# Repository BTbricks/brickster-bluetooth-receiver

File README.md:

# BricksTer &ndash; Bluetooth Receiver

&nbsp;&nbsp;&nbsp;

The BricksTer Bluetooth Receiver lets you wirelessly control your LEGO creations from a smart phone, tablet, or PC. It is compatible with the NXT programmable brick. This repository houses the Eagle CAD schematic and design files for the printed circuit board along with the firmware for the receiver.

## Getting Started

### Part List

Components can be ordered from any distributor (e.g. DigiKey, Mouser, etc).  
[Please see the Bill of Materials for the list of components.](https://github.com/BTbricks/brickster-bluetooth-receiver/blob/master/8884bt%20Remote%20Control%20Receiver/board/BOM.md)

The rev. 2 board can be purchased from OSH Park.  
[Click here to view the OSH Park project page.](https://oshpark.com/shared_projects/jNrizzs2)

### Programming the Board

Once your board is soldered, use the Arduino IDE to load the firmware onto the microcontroller.  
The IDE is available for free and can be downloaded from http://arduino.cc/main/software

#### Setting up the Arduino Environment

The microcontroller is an ATtiny84, which is not regularly supported by the Arduino IDE.  
[Please visit the Arduino support page to learn more about using Arduino with the ATtiny84.](http://playground.arduino.cc/Main/ArduinoOnOtherAtmelChips)

Download the [Attiny 44/45/84/85 files](https://github.com/damellis/attiny/archive/master.zip) and extract them to `{ARDUINO}/hardware/`, where `{ARDUINO}` represents the directory into which the Arduino IDE and supporting files have been installed. Once completed, your directory should look like this:

```
{ARDUINO}
└-hardware
  └-attiny
    ├-boards.txt
    └-variants
      ├-tiny8
      | └-pins_arduino.h
      └-tiny14
        └-pins_arduino.h
```

#### Burning the "Bootloader"

The ATtiny84 comes from the factory running on an internal 1 MHz clock. In order to run the BricksTer firmware, the ATtiny84 must be told to use its interal 8 MHz clock.

* Connect your board to your computer via the programmer
* Apply power to the power-in Power Functions wire
* Open the Arduino IDE
* Ensure you have selected the proper serial port (`Tools > Serial Port`) and can communicate with the microcontroller
* Select `Tools > Board > ATtiny84 (internal 8 Mhz clock)`
* Select `Tools > Burn Bootloader`
* Wait for the programmer to finish, the IDE should display a success message

#### Loading the Firmware

* Connect your board to your computer via the programmer
* Apply power to the power-in Power Functions wire
* Open the Arduino IDE
* Ensure you have selected the proper serial port (`Tools > Serial Port`) and can communicate with the microcontroller
* Select `Tools > Board > ATtiny84 (internal 8 Mhz clock)`
* Open the firmware file, [`brickster8884bt.ino`](https://github.com/BTbricks/brickster-bluetooth-receiver/blob/master/8884bt%20Remote%20Control%20Receiver/firmware/brickster8884bt.ino)
* Click the Upload button on the Arduino IDE (circle with a right-pointing arrow)
* Wait for the the IDE and programmer to finish, the IDE should display a success message

Note: Use of a Atmel AVRISPmk2 programmer is strongly advised. Other programmers have been known to work, but we can only provide support for the AVRISPmk2.

### File Formats

Design files are created in CadSoft Eagle PCB Design Software.  
A free version of the software can be downloaded from www.cadsoftusa.com

&nbsp;&nbsp;&nbsp;

## Distribution License

Where possible, this project uses the MIT license. [Please see the license file for full details.](https://github.com/BTbricks/brickster-bluetooth-receiver/blob/master/LICENSE)

## Contributing

The project is open to all issues and pull requests.  
If you have any other questions or feedback, please [contact the project maintainers](https://github.com/orgs/BTbricks/members).

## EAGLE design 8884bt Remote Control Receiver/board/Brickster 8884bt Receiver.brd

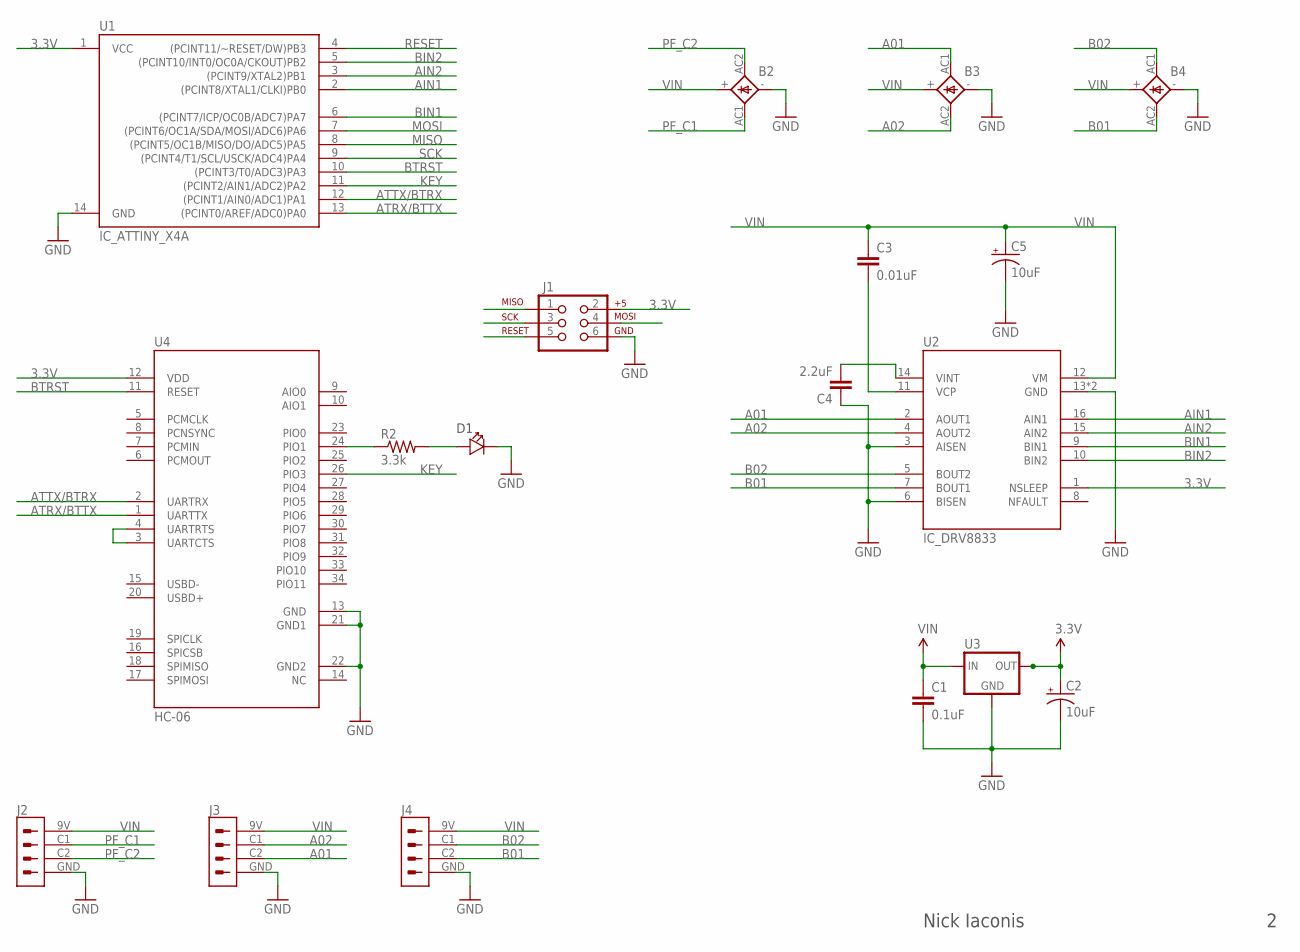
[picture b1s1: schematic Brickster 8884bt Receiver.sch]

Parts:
B2, B3, B4: B_CDBHM240L-HF; MBS-2
C1: 0.1uF; 0805
C2, C5: 10uF; 1206
C3: 0.01uF; 0805
C4: 2.2uF; 0805
D1: LED0805; 0805_POL
J1: AVR_SPI_PRG_6NS; 2X3-NS
J2, J3, J4: CON_PF_SMD; SMD_PF
R2: 3.3k; 0805
U1: IC_ATTINY_X4A; 14S1
U2: IC_DRV8833; PWP_R-PDSO-G16
U3: IC_RT9164A; SOT223
U4: HC-06; BLUETOOTH_SMD

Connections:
3.3V: C2.1 (+), J1.2, U1.1 (VCC), U2.1 (NSLEEP), U3.2 (OUT), U3.4, U4.12 (VDD)
A01: B3.AC1, J3.C2, U2.2 (AOUT1)
A02: B3.AC2, J3.C1, U2.4 (AOUT2)
AIN1: U1.2 ((PCINT8/XTAL1/CLKI)PB0), U2.16 (AIN1)
AIN2: U1.3 ((PCINT9/XTAL2)PB1), U2.15 (AIN2)
ATRX/BTTX: U1.13 ((PCINT0/AREF/ADC0)PA0), U4.1 (UARTTX)
ATTX/BTRX: U1.12 ((PCINT1/AIN0/ADC1)PA1), U4.2 (UARTRX)
B01: B4.AC2, J4.C2, U2.7 (BOUT1)
B02: B4.AC1, J4.C1, U2.5 (BOUT2)
BIN1: U1.6 ((PCINT7/ICP/OC0B/ADC7)PA7), U2.9 (BIN1)
BIN2: U1.5 ((PCINT10/INT0/OC0A/CKOUT)PB2), U2.10 (BIN2)
BTRST: U1.10 ((PCINT3/T0/ADC3)PA3), U4.11 (RESET)
GND: B2.-, B3.-, B4.-, C1.P$2 (2), C2.2 (-), C4.P$1 (1), C5.2 (-), D1.P$1, J1.6, J2.GND, J3.GND, J4.GND, U1.14 (GND), U2.3 (AISEN), U2.6 (BISEN), U2.13 (GND), U2.17 (GND), U3.1 (GND), U4.13 (GND), U4.21 (GND1), U4.22 (GND2)
KEY: U1.11 ((PCINT2/AIN1/ADC2)PA2), U4.26 (PIO3)
LED: R2.P$1 (1), U4.24 (PIO1)
MISO: J1.1, U1.8 ((PCINT5/OC1B/MISO/DO/ADC5)PA5)
MOSI: J1.4, U1.7 ((PCINT6/OC1A/SDA/MOSI/ADC6)PA6)
unnamed: C3.P$2 (2), U2.11 (VCP)
unnamed: C4.P$2 (2), U2.14 (VINT)
unnamed: U4.3 (UARTCTS), U4.4 (UARTRTS)
unnamed: D1.P$2, R2.P$2 (2)
PF_C1: B2.AC1, J2.C1
PF_C2: B2.AC2, J2.C2
RESET: J1.5, U1.4 ((PCINT11/~RESET/DW)PB3)
SCK: J1.3, U1.9 ((PCINT4/T1/SCL/USCK/ADC4)PA4)
VIN: B2.+, B3.+, B4.+, C1.P$1 (1), C3.P$1 (1), C5.1 (+), J2.9V, J3.9V, J4.9V, U2.12 (VM), U3.3 (IN)

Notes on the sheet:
Nick Iaconis

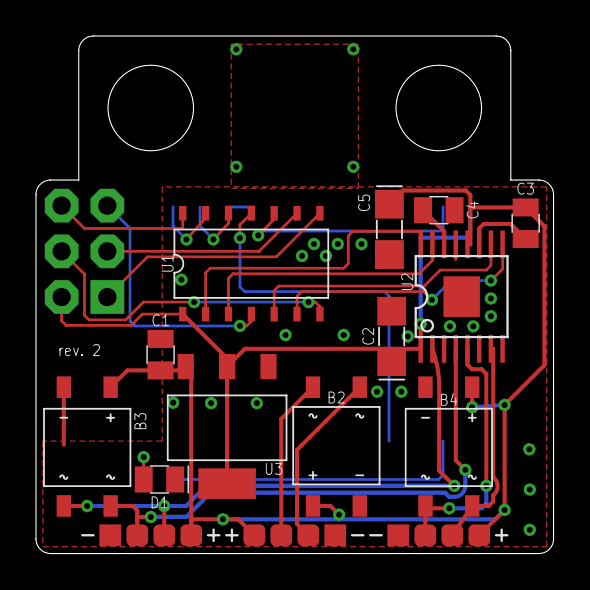
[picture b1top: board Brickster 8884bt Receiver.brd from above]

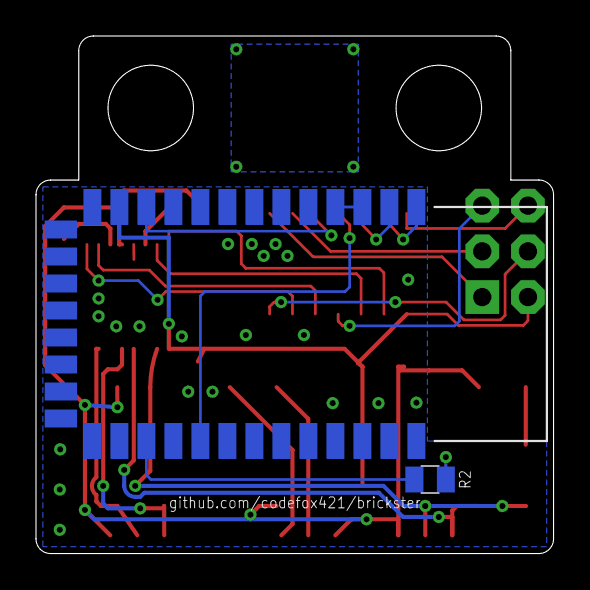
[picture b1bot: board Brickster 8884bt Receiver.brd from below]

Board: 2 copper layers, 28.8 x 28.8 mm, 20 parts (3 on the bottom side), 26 nets.

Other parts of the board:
LOGO1, LOGO2: OSHW-LOGOM; OSHW-LOGO-M-MASK

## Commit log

2014-02-27 Clear bluetooth-receiver history in order to merge with android into master
2014-03-19 Only build the master branch
2014-03-19 Remove readme from bluetooth branch
2014-03-19 Include gitignore in bluetooth branch
2014-03-20 Update receiver to revision 1a
2014-03-20 Update board & schematic images
2014-04-10 Implement command architecture described at http://codepen.io/anon/pen/nxhzt/ Prepare firmware for switch to drv8833 motor driver chip
2014-04-28 Add drv8833 to library and schematic
2014-05-11 Add HC-06
2014-05-12 Route rev. 2 board
    Need to change OSH logo to t/b-stop
2014-05-12 Change regulator manufacturer
2014-06-12 Route rev. 2 board
    Use SMD pads for Power Functions connections
    (threading PF wire through tiny vias is too difficult)
2014-06-29 Update firmware for rev. 2 board
2014-06-29 Update schematic/board PNGs
2014-06-29 Uncomment missing lines necessary for rev. 2
2014-07-16 Fix run-away-at-same-speed bug
2014-07-16 Remove unreferenced variable
2014-08-11 Fix bug when braking with drv8833
2014-08-14 Increase baudrate to 57600
2014-08-14 Write literal bytes instead of decimal representations
2014-08-21 Use default 9600 baud rate
    The baud rate of 57600 was causing some stability issues. The ATtiny84's
    internal oscillator is too sensitive to the environment (mostly
    temperature) to use such a high rate. The default of 9600 should be just
    fine now that only one single byte is being sent for every byte
    received.
2014-08-21 Don't restart the Bluetooth module at boot
    Since we aren't changing the baud rate, we no longer need to reset the
    Bluetooth module at boot
2015-07-20 Move ino file into a sketch directory
    This will allow Arduino IDE to open it in place.
2015-07-20 Ensure Bluetooth module is enabled on boot
    Without explicitly writing HIGH to the !BTRST line, the module could be
    in reset mode.
2016-02-15 Update gitignore
2016-02-15 Update library
2016-02-15 Update DRC file

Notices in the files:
parts and their libraries:
SparkFun-Connectors: Licensing: CC v3.0 Share-Alike You are welcome to use this library for commercial purposes.
